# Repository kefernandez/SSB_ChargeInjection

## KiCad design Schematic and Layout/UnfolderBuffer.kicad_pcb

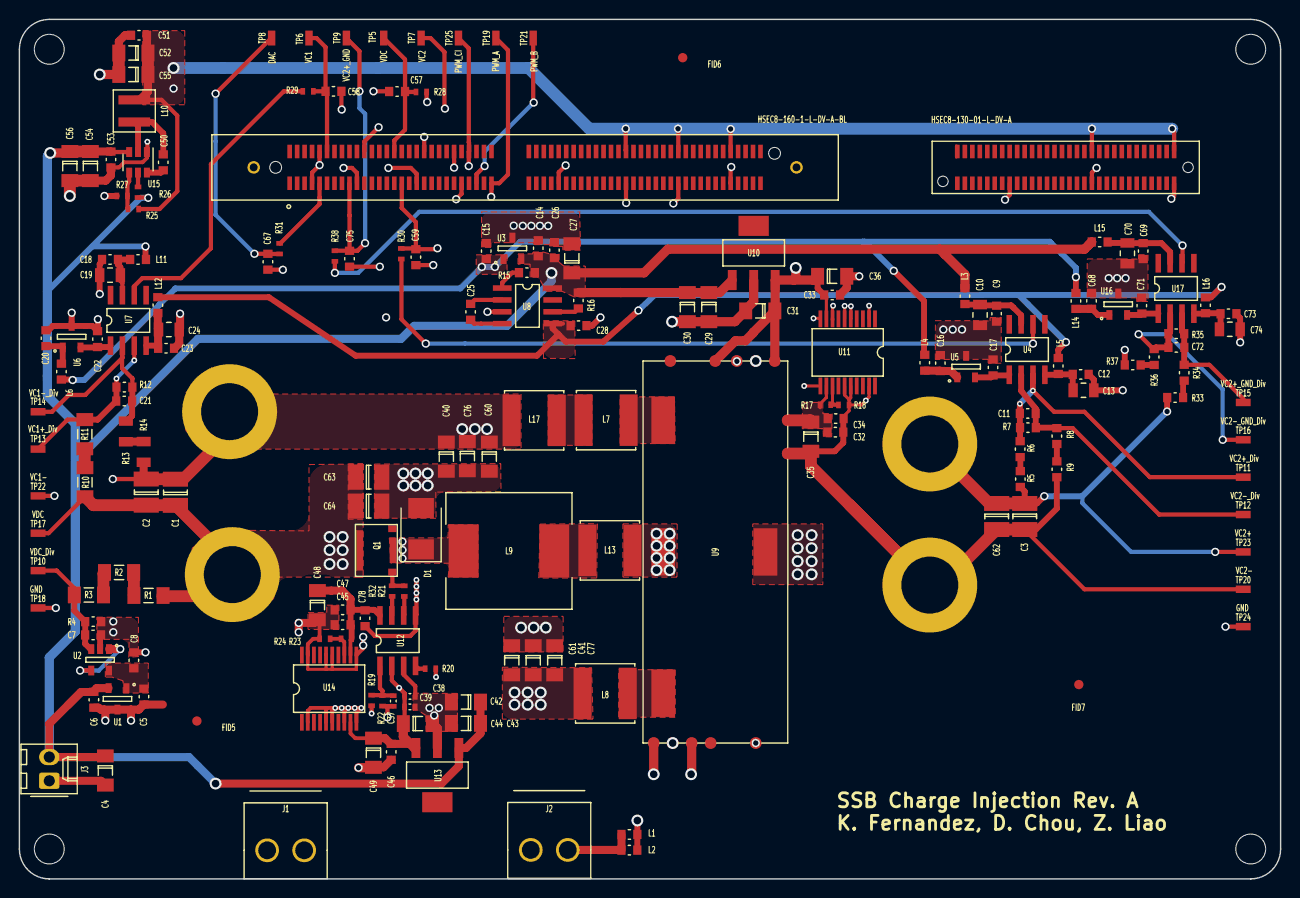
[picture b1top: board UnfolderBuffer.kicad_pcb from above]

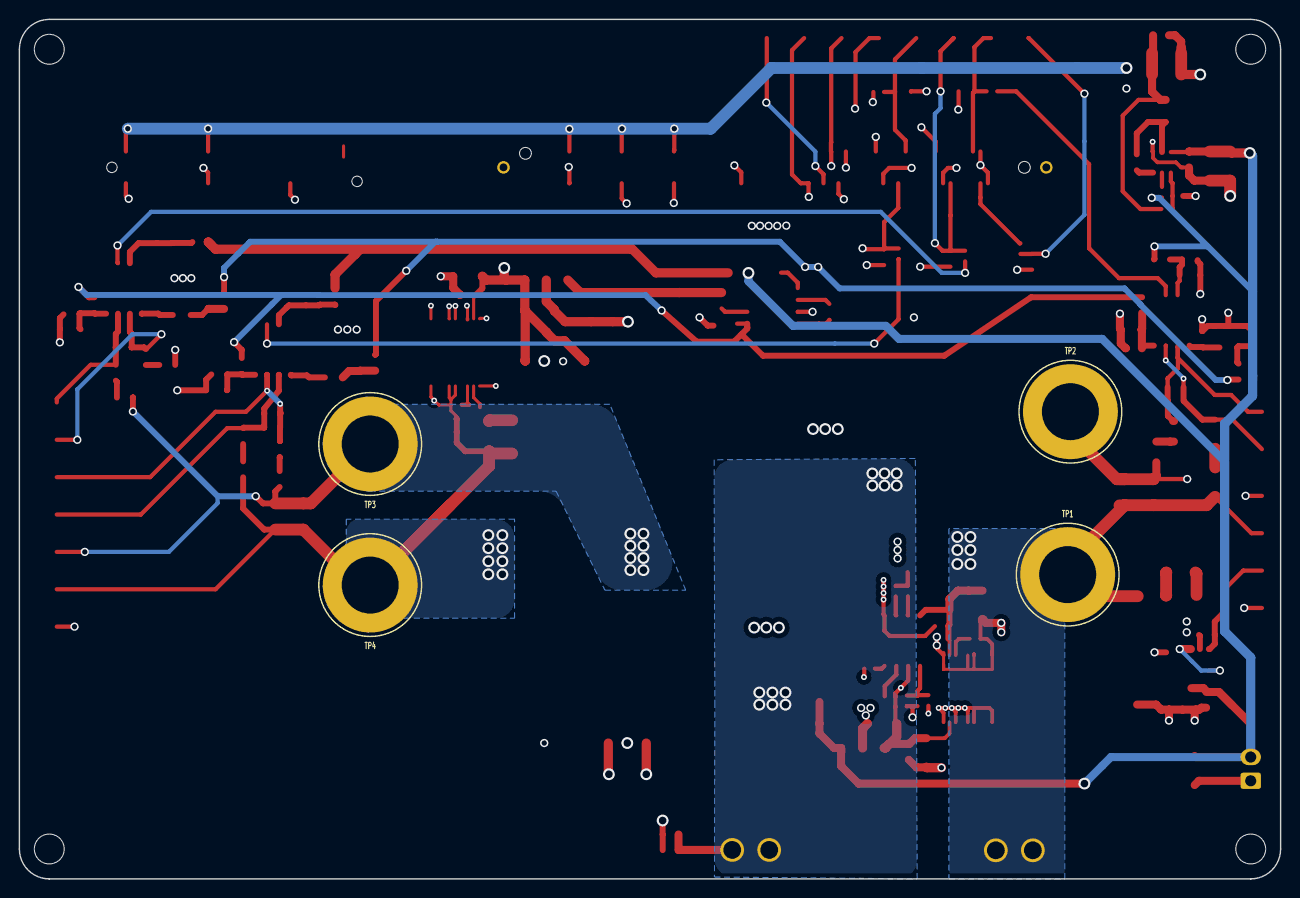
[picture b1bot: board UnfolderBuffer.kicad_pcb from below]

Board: 4 copper layers, 135.0 x 92.0 mm, 187 parts (4 on the bottom side), 75 nets.

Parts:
C1, C2: C1_sense; C_1210
C3, C62: C2_sense; C_1210
C4: 1uF; C_1206
C5, C6, C8, C9, C12, C14, C15, C16, C17, C18, C20, C22, C23, C26, C32, C45, C67, C68, C69, C71, C73, C75, C78: 1uF; C_0603
C7: 1000pF; C_0603
C10, C13, C19, C24, C70, C74: 10uF; C_0805
C11, C21, C72: 100pF; C_0603
C25, C28: 10uF; C_0603
C27, C29, C31, C35, C36, C42, C44, C48, C49, C54, C56: 10uF; C_1206
C30, C43: 0.1uF; C_1206
C33, C34, C46, C47, C50, C51, C53, C57, C59: 0.1uF; C_0603
C37: 100pF; C_0402
C38: 1uF; C_0402
C39: 0.1uF; C_0402
C40, C41, C60, C61, C76, C77: C3; C_1206
C52, C55: 22uF; C_1206
C58: .01uF; C_0603
C63, C64: Vbus_loop; C_1210
D1: D; D_SMB
FID1, FID2, FID3, FID4: Stand; MountingHole_3.2mm_M3
FID5, FID6, FID7: FID; Fiducial_1mm_Dia_2.54mm_Outer_CopperTop
J1, J2: Conn_01x02; MTA156_2pin
J3: Conn_01x02; Molex_KK-254_AE-6410-02A_1x02_P2.54mm_Vertical
J4: HSEC8-160-1-L-DV-A-BL; SAMTEC_HSEC8-160-01-L-DV-A-BL
J5: HSEC8-130-01-L-DV-A; SKT-60_flipped
L1, L2: Bead; R_0603
L3, L4, L5, L6, L11, L12, L14, L15, L16: Ferrite; C_0603
L7, L8, L17: 47uH; XAL7070
L9: 100uH; MSS1210
L10: 4.7uH; XEL4030
L13: 100uH; XAL7070
Q1: NFET_GaNSystems; GS66506T
R1, R2, R3: 470k; R_1206
R4, R15, R16: 10k; R_0603
R5, R6, R8, R9, R33, R34, R36, R37: 33k; R_0603
R7, R12, R35: 2k; R_0603
R10, R11: 44.2k; R_1206
R13, R14: 44.2k; R_0805
R17, R23: 30.9k; R_0402
R18, R24: 9.53k; R_0402
R19, R28, R29, R31, R38: 150; R_0402
R20, R32: 0; R_0402
R21: 15; R_0402
R22, R26, R27: 10k; R_0402
R25: 54.9k; R_0402
R30: 500; R_0402
TP1, TP2, TP3, TP4: TP; Banana_Jack_1Pin
TP5, TP6, TP7, TP8, TP9, TP10, TP11, TP12, TP13, TP14, TP15, TP16, TP17, TP18, TP19, TP20, TP21, TP22, TP23, TP24, TP25: TestPoint; 0603 TP
U1: TLV760 - 3.3V; SOT-23
U2: LTC2050_+; SOT-23-5
U3: TLV760; SOT-23
U4, U7, U17: LT1990; SOIC-8
U5, U6, U16: REF3012; SOT-23
U8: LTC1144; SOIC-8
U9: FullBridgeCell; Buffer Full Bridge
U10, U13: LM2937xMP; SOT223-4
U11, U14: ADuM5010; SSOP-20_Wide
U12: Si8271; SOIC-8
U15: TPS562200; SOT-23-6

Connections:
6V5: C4.1, C6.1, C14.1, C26.1, C27.1, C29.1, C30.1, C42.1, C43.1, C53.1, C54.1, C56.1, J3.2, L3.1, L11.1, L15.1, R15.2, R16.1, R26.2, U1.2, U3.2, U8.8, U10.1, U13.1, U15.3
/C1-: C1.2, C2.2, C40.1, C41.1, C60.1, C61.1, C76.1, C77.1, L17.2, R14.2, TP2.1, TP22.1
/C2+: C3.1, C62.1, L13.2, R5.1, R33.1, TP3.1, TP23.1, U9.10
/C2-: C3.2, C32.2, C34.2, C35.2, C62.2, R9.2, R18.2, TP4.1, TP20.1, U9.11, U9.13, U11.11, U11.15, U11.16, U11.19
/CI/En_CI: R20.2, U12.4
/CI/Gate_CI: Q1.G, R21.1, R32.1
/CI/L_Jumper: L9.2, L13.1
/CI/PWM_CI: C37.1, R19.2, R22.1, U12.1
/CI/VDDISO2: C45.1, C47.1, C48.1, C78.1, R23.1, U12.8, U14.12
/CI/VDD_Logic_CI: C38.1, C39.1, C44.1, C46.1, C49.1, R20.1, U12.2, U13.3, U14.9
/CI/Vo_high: R21.2, U12.7
/CI/Vo_low: R32.2, U12.6
/CI/sheet5FF6C3C6/Sel: R23.2, R24.1, U14.13
/INCI: J4.50, R19.1, TP25.1
/MCU_Connector/5V: C51.1, C52.1, C55.1, J4.84, J4.98, J4.112, J5.38, J5.60, L10.2, R25.2
/MCU_Connector/Buck_Bst: C50.2, U15.6
/MCU_Connector/Buck_FB: R25.1, R27.2, U15.4
/MCU_Connector/Buck_Sw: C50.1, L10.1, U15.2
/MCU_Connector/DACOUT: J4.9, R31.1
/MCU_Connector/DACOUT_probe: C67.1, R31.2, TP8.1
/MCU_Connector/En_Buck: R26.1, U15.5
/MCU_Connector/Vc1: C58.1, J4.12, R29.2, TP6.1
/MCU_Connector/Vc2: C59.1, J4.31, R30.2, TP7.1
/MCU_Connector/Vc2_GND: C75.1, J4.17, R38.2, TP9.1
/MCU_Connector/Vdc: C57.1, J4.30, R28.2, TP5.1
/SSB/GND_L_FB: L8.1, U9.9
/SSB/ISODCDC/Sel: R17.2, R18.1, U11.13
/SSB/LC1_FB: L7.1, U9.8
/SSB/VDDISO1: C32.1, C34.1, C35.1, R17.1, U9.12, U11.12
/SSB/VDD_Logic_FB: C31.1, C33.1, C36.1, U9.1, U9.6, U10.3, U11.9
/Sci_Source: C45.2, C47.2, C48.2, C78.2, D1.1, L9.1, Q1.S, R24.2, U12.5, U14.11, U14.15, U14.16, U14.19
/VC1_SENSE: R29.1, U7.6
/VC2_GND_SENSE: R38.1, U17.6
/VC2_SENSE: R30.1, U4.6
/VCSense/1V25_VC1SENSE: C22.1, U6.2, U7.1
/VCSense/1V25_VC2SENSE: C17.1, U4.1, U5.2
/VCSense/1V25_VC2_GND_SENSE: C71.1, U16.2, U17.1
/VCSense/5V_VC1SENSE_FIL: C20.1, L6.2, U6.1
/VCSense/5V_VC2SENSE_FIL: C16.1, L4.2, U5.1
/VCSense/5V_VC2_GND_SENSE_FIL: C68.1, L14.2, U16.1
/VCSense/5V_VCSENSE: C15.1, L4.1, L6.1, L14.1, U3.1
/VCSense/6V5_C1_FIL_SENSE: C18.1, C19.1, L11.2, U7.7
/VCSense/6V5_C2_FIL_SENSE: C9.1, C10.1, L3.2, U4.7
/VCSense/6V5_C2_GND_FIL_SENSE: C69.1, C70.1, L15.2, U17.7
/VCSense/-6V5_C1_FIL_SENSE: C23.2, C24.2, L12.1, U7.4
/VCSense/-6V5_C2_FIL_SENSE: C12.2, C13.2, L5.1, U4.4
/VCSense/-6V5_C2_GND_FIL_SENSE: C73.2, C74.2, L16.1, U17.4
/VCSense/-6V5_VCSENSE: C28.1, L5.2, L12.2, L16.2, U8.5
/VCSense/V+_C1: C21.1, R11.2, R12.1, TP13.1, U7.3
/VCSense/V+_C2: C11.1, R6.2, R7.1, TP11.1, U4.3
/VCSense/V+_C2_GND: C72.1, R34.2, R35.1, TP15.1, U17.3
/VCSense/V-_C1: C21.2, R12.2, R13.1, TP14.1, U7.2
/VCSense/V-_C2: C11.2, R7.2, R8.1, TP12.1, U4.2
/VCSense/V-_GND_C2: C72.2, R35.2, R36.1, TP16.1, U17.2
/VDC: C1.1, C2.1, C63.1, C64.1, J1.1, J1.2, Q1.D, R1.1, R10.1, TP1.1, TP17.1
/VDC/HV1_DIV: C7.1, R3.2, R4.1, TP10.1, U2.3
/VDC_SENSE: R28.1, U2.1, U2.4
/VDD_Logic_HVSense: C5.1, C8.1, U1.1, U2.5
/~INA: J4.55, TP19.1, U9.2
/~INB: J4.51, TP21.1, U9.4
GND: C4.2, C5.2, C6.2, C7.2, C8.2, C9.2, C10.2, C12.1, C13.1, C14.2, C15.2, C16.2, C17.2, C18.2, C19.2, C20.2, C22.2, C23.1, C24.1, C26.2, C27.2, C28.2, C29.2, C30.2, C31.2, C33.2, C36.2, C37.2, C38.2, C39.2, C42.2, C43.2, C44.2, C46.2, C49.2, C51.2, C52.2, C53.2, C54.2, C55.2, C56.2, C57.2, C58.2, C59.2, C67.2, C68.2, C69.2, C70.2, C71.2, C73.1, C74.1, C75.2, J3.1, J4.7, J4.10, J4.19, J4.22, J4.35, J4.38, J4.46, J4.47, J4.65, J4.83, J4.97, J4.111, J5.15, J5.37, J5.59, L1.2, L2.2, R4.2, R22.2, R27.1, R37.2, TP18.1, TP24.1, U1.3, U2.2, U3.3, U5.3, U6.3, U8.3, U9.7, U10.2, U11.2, U11.5, U11.6, U11.8, U11.10, U12.3, U13.2, U14.2, U14.5, U14.6, U14.8, U14.10, U15.1, U16.3
GNDPWR: C40.2, C41.2, C60.2, C61.2, C63.2, C64.2, C76.2, C77.2, D1.2, J2.1, J2.2, L1.1, L2.1, L8.2
unnamed: C25.1, U8.2
unnamed: C25.2, U8.4
unnamed: L7.2, L17.1
unnamed: R1.2, R2.1
unnamed: R2.2, R3.1
unnamed: R5.2, R6.1
unnamed: R8.2, R9.1
unnamed: R10.2, R11.1
unnamed: R13.2, R14.1
unnamed: R15.1, U8.1
unnamed: R16.2, U8.6
unnamed: R33.2, R34.1
unnamed: R36.2, R37.1

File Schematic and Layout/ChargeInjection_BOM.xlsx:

References | Quantity | Quanitity Ordered | Value | Footprint | Max Voltage/Current | Supplier Part Number | MFG Part No. | Supplier | Temp Coefficient | Voltage Rating |  | Notes
C37 | 1 | 50 | 100pF | C_0402 | 5V | 478-12641-1-ND | 04025C101JAT2A | Digikey | X7R | 50V
C38 | 1 | 50 | 1uF | C_0402 | 5V | 1276-1513-1-ND | CL05B105KQ5NQNC | Digikey | X7R | 6.3V
C39 | 1 | 50 | 0.1uF | C_0402 | 5V | 1276-1002-1-ND | CL05B104KP5NNNC | Digikey | X7R | 10V
C5, C6, C8, C9, C12, C14, C15, C16, C17, C18, C20, C22, C23, C26, C32, C45, C68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 | 21 | 100 | 1uF | C_0603 |  | 1276-1946-1-ND | CL10B105KP8NNNC | Digikey | X7R | 10V
C11, C21, C57, C58, C59, C67, C72, C75 | 8 | 50 | 100pF | C_0603 |  | 1276-1908-1-ND | CL10B101KB8NFNC | Digikey | X7R | 50V
C33, C34, C46, C47, C50, C51, C53 | 7 | 50 | 0.1uF | C_0603 |  | 1276-CL10B104KB8NNNLCT-ND | CL10B104KB8NNNL | Digikey | X7R | 50V
C25, C28 | 2 | 50 | 10uF | C_0603 | 6.5V | 490-14461-1-ND | GRM188D71A106KA73D | Digikey | X7T | 10V |  | Pricey
C7 | 1 | 50 | 1000pF | C_0603 | 2.8V | 1276-1018-1-ND | CL10B102KB8NNNC | Digikey | X7R | 50V
C10, C13, C19, C24, C70, C74 | 6 | 50 | 10uF | C_0805 | 6.5V | 1276-1764-1-ND | CL21B106KPQNNNE | Digikey | X7R | 10V
C27, C29, C31, C35, C36, C42, C44, C48, C49, C54, C56 | 11 | 50 | 10uF | C_1206 | 6.5V | 1276-6641-1-ND | CL31B106MOHNNNE | Digikey | X7R | 16V
C40, C41, C60, C61, C76, C77 | 6 | 50 | 1uF (C3) | C_1206 | 85V | 1276-1838-1-ND | CL31B105KCHNNNE | Digikey | X7R | 100V
C30, C43 | 2 | 30 | 0.1uF | C_1206 | 6.5V | 732-8086-1-ND | CAP CER 0.1UF 10V X7R 1206 | Digikey | X7R | 10V |  | Could have made this an 0805 or an 0603, will order some 0805s as well
C52, C55 | 2 | 30 | 22uF | C_1206 | 5V | 1276-3148-1-ND | CL31B226MPHNNNE | Digikey | X7R | 10V
C4 | 1 | 30 | 1uF | C_1206 | 6.5V | 478-12854-1-ND | 1206ZC105KAT2A | Digikey | X7R | 10V
C1, C2 | 2 | 50 | 0.1uF (C1_sense) | C_1210 | 500V | 399-15981-1-ND | C1210C104KBRACAUTO | Digikey | X7R | 630V
C3, C62 | 2 | 30 | 1uF (C2_sense) | C_1210 | 100V | 1276-1812-1-ND | CL32B105KCJNNNE | Digikey | X7R | 100V
C63, C64 | 2 |  | 0.1uF (Vbus_loop) | C_1210 | 400V | 399-15981-1-ND | C1210C104KBRACAUTO | Digikey | X7R | 630V
R28, R29, R30, R31, R38 | 5 | 30 | 499 | R_0402 |  | P499DCCT-ND | ERA-2AEB4990X | Digikey |  | 1/16W
R22, R26, R27 | 3 | 30 | 10k | R_0402 |  | MCS0402-10.0K-MFCT-ND | MCS0402MC1002FE000 | Digikey |  | 1/10W
R17, R23 | 2 | 20 | 30.9k | R_0402 | 16nA, 0.5 mW | P18022CT-ND | ERA-2ARB3092X | Digikey |  | 1/16W | 1E-3
R18, R24 | 2 | 20 | 9.53k | R_0402 | 16nA, 0.2mW | P17916CT-ND | ERA-2APB9531X | Digikey |  | 1/16W | 1E-3
R20, R32 | 2 | 30 | 0 | R_0402 |  | 541-0.0JCT-ND | CRCW04020000Z0ED | Digikey |  | 1/16W
R19 | 1 | 30 | 150 | R_0402 |  | P150DCCT-ND | ERA-2AEB151X | Digikey |  | 1/16W | 1E-3
R21 | 1 | 30 | 15 | R_0402 |  | P15DDCT-ND | ERA-2AKD150X | Digikey |  | 1/16W | 5.0000000000000001E-3
R25 | 1 | 20 | 54.9k | R_0402 |  | YAG1452CT-ND | RT0402BRD0754K9L | Digikey |  | 1/16W | 1E-3
R5, R6, R8, R9, R33, R34, R36, R37 | 8 | 25 | 33k | R_0603 | 0.05W | P20143CT-ND | ERJ-PB3B3302V | Digikey |  | 1/5W | 1E-3
R4, R15, R16 | 3 | 30 | 10k | R_0603 | 0.8mW | P10KDBCT-ND | ERA-3AEB103V | Digikey |  | 1/10W | 1E-3
R7, R12, R35 | 3 | 30 | 2k | R_0603 | 0.5mW | RG16P2.0KBCT-ND | RG1608P-202-B-T5 | Digikey |  | 1/10W | 1E-3
R13, R14 | 2 | 20 | 16k | R_0805 | 0.04W | P16KDACT-ND | ERA-6AEB163V | Digikey |  | 1/8W | 1E-3
R1, R2, R3 | 3 | 30 | 470k | R_1206 | 0.04W | P470KBCCT-ND | ERA-8AEB474V | Digikey |  | 1/4W | 1E-3
R10, R11 | 2 | 30 | 150k | R_1206 | 0.35W | RHM150KAFCT-ND | ESR18EZPF1503 | Digikey |  | 1/2W | 1E-3
L3, L4, L5, L6, L11, L12, L14, L15, L16 | 9 | 50 | Ferrite | C_0603 | 1.2E-4 | 732-1592-1-ND | 742792641 | Digikey |  | 2A
L9 | 1 | 10 | 100uH | MSS1210 | 1.2A | 994-MSS1210-104KEB | MSS1210-104KEB | Mouser
L1, L2 | 2 |  | Bead | R_0603 |  | 732-1592-1-ND | 742792641 | Digikey
L7, L8, L17 | 3 | 20 | 47uH | XAL7070 |  | XAL7070-473MEC | XAL7070-473MEC | Coilcraft
L13 - DNP - Jumper | 0 | X | 100uH | XAL7070 |  |  |  | N/A
L10 - Derek has several in lab | 1 | X | 4.7uH | XEL4030 |  | 994-XAL7070-472MEB | XAL7070-472MEB | N/A
D1 | 1 | 15 | D | D_SMB |  | MURS160T3GOSCT-ND | MURS160T3G | Digikey
U9 | 1 | X | FullBridgeCell | Buffer Full Bridge
U4, U7, U17 | 3 | 12 | LT1990 | SOIC-8 |  | LT1990CS8#PBF-ND | LT1990CS8#PBF | Digikey
U8 | 1 | 6 | LTC1144 | SOIC-8 |  | LTC1144CS8#PBF-ND | LTC1144CS8#PBF | Digikey
U12 | 1 | 10 | Si8271 | SOIC-8 |  | 336-3533-5-ND | SI8271GB-IS | Digikey
U5, U6, U16 | 3 | 15 | REF3012 | SOT-23 |  | 296-32213-1-ND | REF3012AIDBZR | Digikey
U1, U3 | 2 | 12 | TLV760 - 5V | SOT-23 |  | 296-48333-1-ND | TLV76050DBZR | Digikey
 | 2 | 12 | TLV760 - 3.3V | SOT-23 |  | 296-47016-1-ND | TLV76033DBZT | Digikey
U2 | 1 | 6 | LTC2050_+ | SOT-23-5 |  | LTC2050CS8#PBF-ND | LTC2050CS8#PBF | Digikey
U15 | 1 | 10 | TPS562200 | SOT-23-6 |  | 296-39631-1-ND | TPS562200DDCR | Digikey
U10, U13 | 2 | 10 | LM2937xMP | SOT223-4 |  | LM2937IMP-5.0/NOPBCT-ND | LM2937IMP-5.0/NOPB | Digikey
U11, U14 | 2 | 6 | ADuM5010 | SSOP-20_Wide |  | ADUM5010ARSZ-RL7CT-ND | ADUM5010ARSZ-RL7 | Digikey
TP5, TP6, TP7, TP8, TP9, TP10, TP11, TP12, TP13, TP14, TP15, TP16, TP17, TP18, 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 | 21 | 80 | TestPoint | 0603 TP |  | A106145CT-ND | RCU-0C | Digikey
TP1, TP2, TP3, TP4 | 4 | 10 | TP | Banana_Jack_1Pin |  | BKCT2232-2-ND | CT2232-2 | Digikey
Q1 | 1 | 10 | NFET_GaNSystems | GS66506T |  | 499-GS66506T-MR | GS66506T-MR | Mouser
J1, J2 | 2 | 6 | Conn_01x02 | MTA156_2pin |  | A105038-ND | 3-641209-4 | Digikey
J3 | 1 | 5 | Conn_01x02 | Molex_KK-254_AE-6410-02A_1x02_P2.54mm_Vertical |  | A26564-ND | 1-87215-0 | Digikey
J4 | 1 | 2 | HSEC8-160-1-L-DV-A-BL | SAMTEC_HSEC8-160-01-L-DV-A-BL |  | SAM9083-ND | HSEC8-160-01-L-DV-A-BL | Digikey
J5 | 1 | 2 | HSEC8-130-01-L-DV-A | SKT-60_flipped |  | SAM9080-ND | HSEC8-130-01-L-DV-A | Digikey
C_1 | 2 | 2 | C1 |  |  | 495-3956-ND | B32776G4406K000
C_2 | 3 | 3 | C2 |  |  | 495-4131-ND | B32524Q1686K000
MCU | 1 | 1 | ControlCARD |  |  | 296-46777-ND | TMDSCNCD28379D

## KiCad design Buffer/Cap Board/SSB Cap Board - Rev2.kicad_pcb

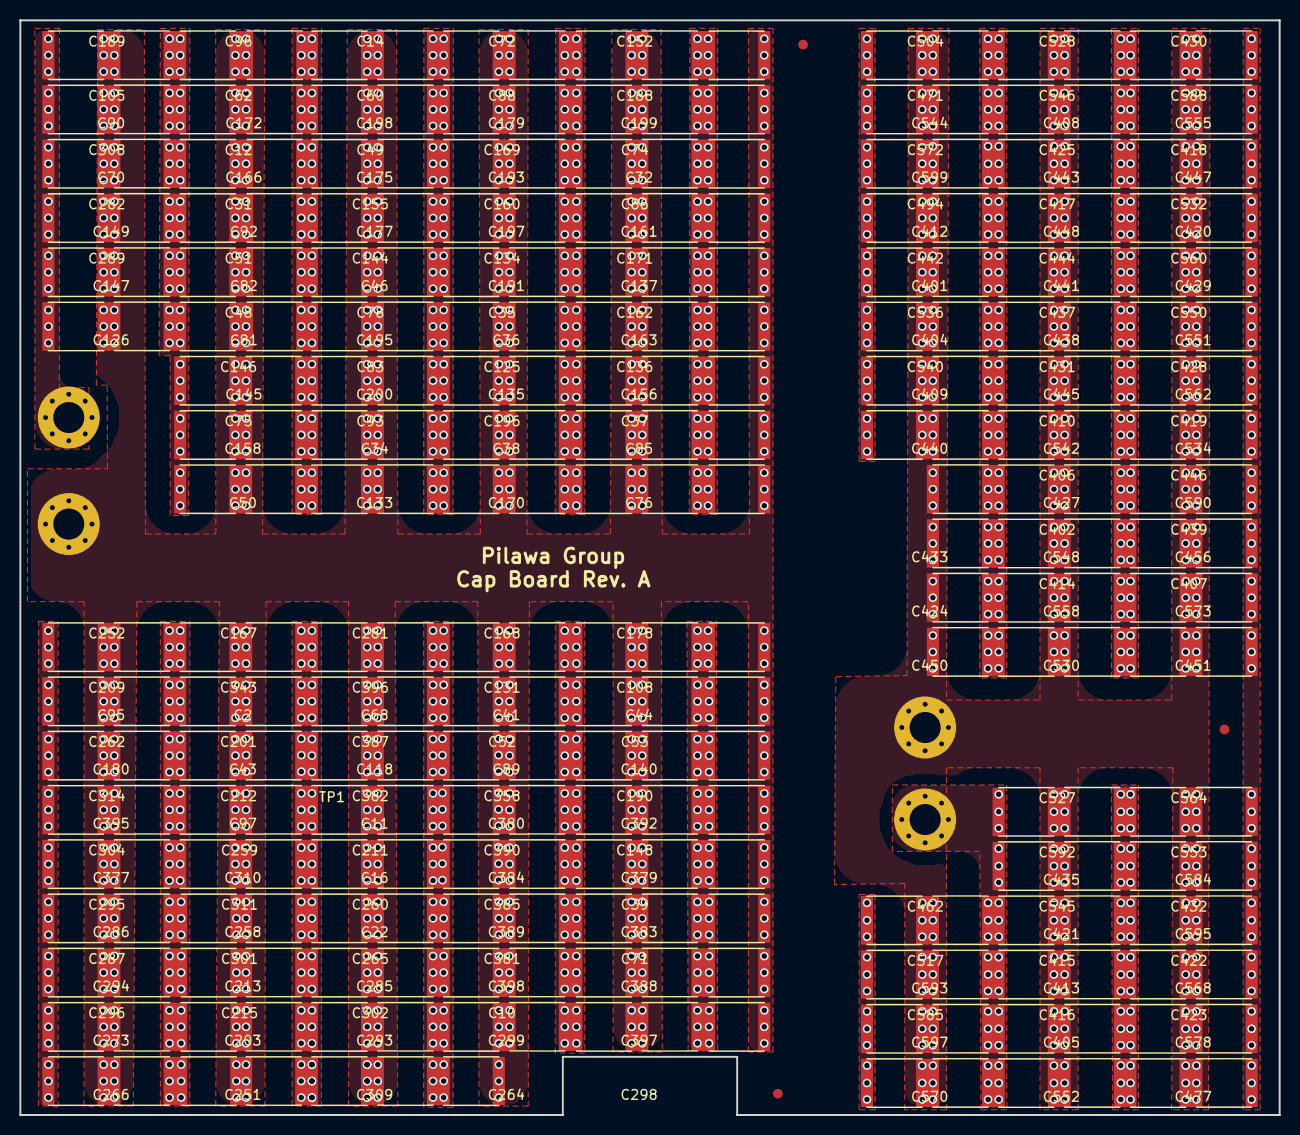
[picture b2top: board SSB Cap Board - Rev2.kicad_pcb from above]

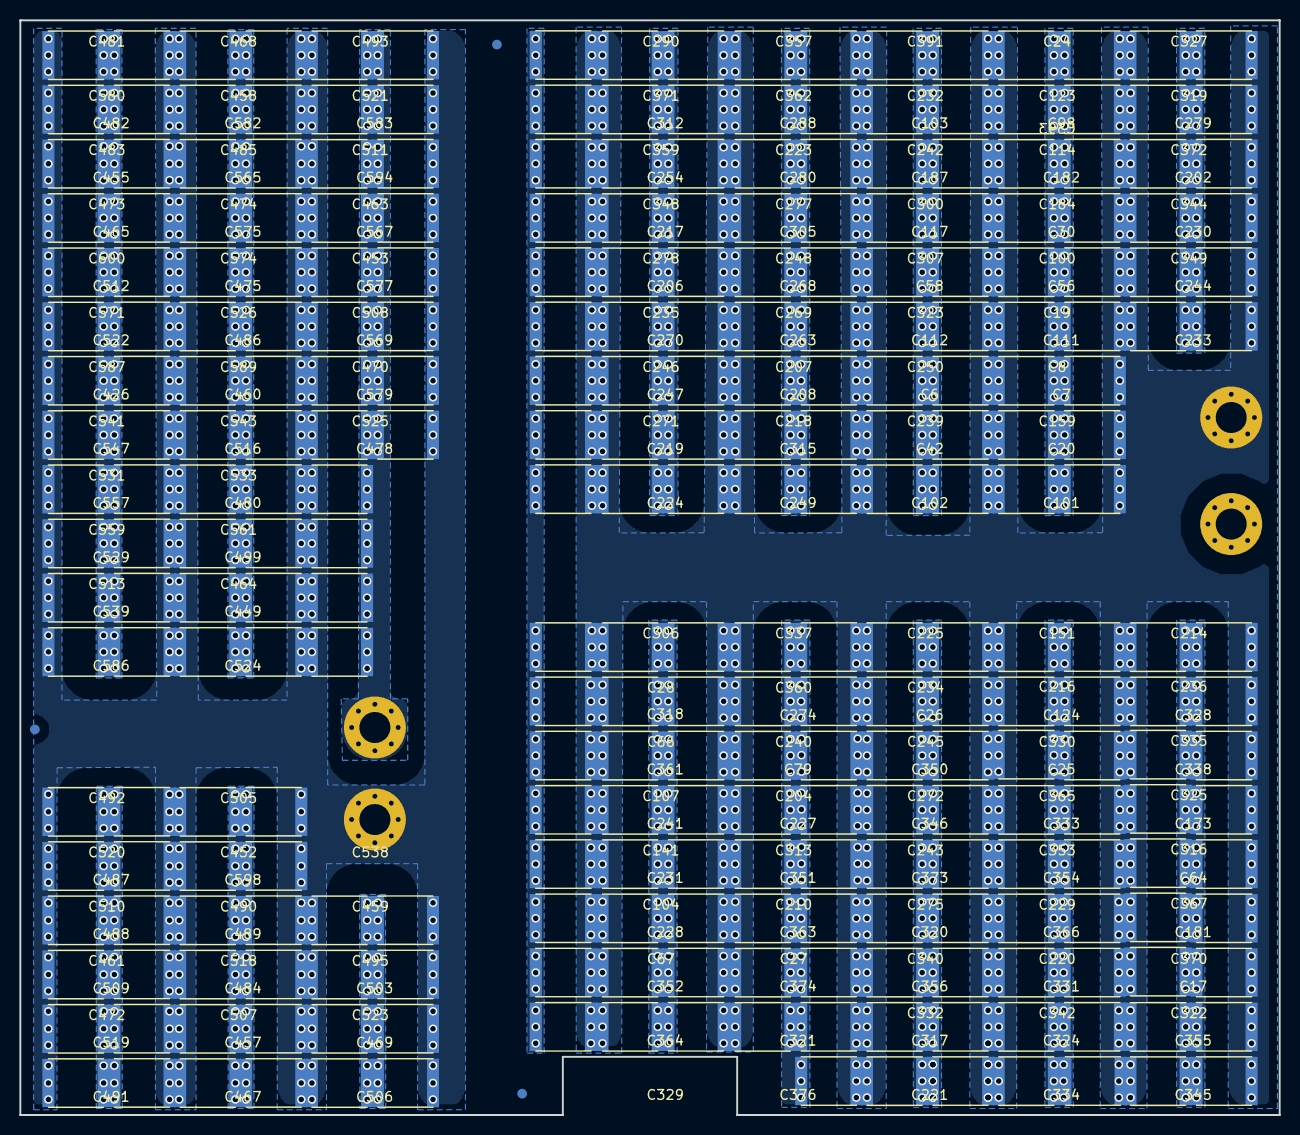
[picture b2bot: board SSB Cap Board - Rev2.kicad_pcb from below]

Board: 2 copper layers, 130.0 x 113.0 mm, 580 parts (288 on the bottom side), 4 nets, no tracks yet.

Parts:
C2, C3, C4, C5, C6, C7, C8, C9, C10, C11, C12, C14, C15, C16, C17, C18, C19, C20, C21, C22, C23, C24, C25, C26, C27, C28, C30, C31, C32, C34, C35, C36, C37, C38, C39, C40, C41, C42, C43, C44, C45, C46, C48, C49, C50, C51, C52, C53, C54, C56, C57, C58, C59, C60, C61, C62, C63, C64, C66, C67, C68, C69, C70, C71, C72, C74, C75, C76, C77, C78, C79, C80, C81, C82, C83, C84, C85, C86, C87, C88, C89, C90, C91, C92, C93, C94, C95, C96, C97, C98, C99, C100, C101, C102, C103, C104, C105, C106, C107, C108, C109, C111, C112, C113, C114, C117, C118, C119, C120, C121, C122, C123, C124, C125, C126, C129, C130, C131, C132, C133, C134, C135, C136, C137, C140, C141, C142, C143, C144, C145, C146, C147, C148, C149, C150, C151, C152, C154, C155, C156, C157, C158, C159, C160, C161, C162, C163, C164, C166, C167, C168, C169, C170, C171, C172, C173, C174, C175, C176, C177, C178, C179, C180, C181, C182, C183, C184, C185, C186, C187, C188, C189, C190, C191, C193, C194, C195, C196, C197, C198, C199, C200, C201, C202, C203, C204, C205, C206, C207, C208, C209, C210, C211, C212, C213, C214, C215, C216, C217, C218, C219, C220, C221, C223, C224, C225, C226, C227, C228, C229, C230, C231, C232, C233, C234, C235, C236, C237, C238, C239, C240, C241, C242, C243, C244, C245, C246, C247, C248, C249, C250, C251, C252, C254, C255, C256, C257, C258, C259, C260, C261, C262, C263, C264, C265, C266, C267, C268, C269, C270, C271, C272, C273, C274, C275, C276, C277, C278, C279, C280, C281, C282, C283, C285, C286, C287, C288, C289, C290, C291, C292, C293, C294, C295, C296, C297, C298, C299, C300, C301, C302, C303, C304, C305, C306, C307, C308, C309, C310, C311, C312, C313, C314, C315, C316, C317, C318, C319, C320, C321, C322, C323, C324, C325, C326, C327, C328, C329, C330, C331, C332, C333, C334, C335, C336, C337, C338, C339, C340, C341, C342, C343, C344, C345, C346, C347, C348, C349, C350, C351, C352, C353, C354, C355, C356, C357, C358, C359, C360, C361, C362, C363, C364, C365, C366, C367, C368, C369, C370, C371, C372, C373, C374, C375, C376, C377, C378, C379, C380, C381, C382, C383, C384, C385, C387, C388, C389, C390, C391, C392, C393, C394, C395, C396, C397, C398, C401, C402, C403, C404, C405, C406, C407, C408, C409, C410, C411, C412, C413, C414, C415, C416, C417, C418, C419, C420, C421, C422, C423, C424, C425, C426, C427, C428, C429, C430, C431, C432, C433, C434, C435, C436, C437, C438, C439, C440, C441, C442, C443, C444, C445, C446, C447, C448, C449, C450, C451, C452, C453, C454, C455, C456, C457, C458, C459, C460, C461, C462, C463, C464, C465, C466, C467, C468, C469, C470, C471, C472, C473, C474, C475, C476, C477, C478, C479, C480, C481, C482, C483, C484, C485, C486, C487, C488, C489, C490, C491, C492, C493, C494, C495, C496, C497, C498, C499, C500, C501, C502, C503, C504, C505, C506, C507, C508, C509, C510, C511, C512, C513, C514, C515, C516, C517, C518, C519, C520, C521, C522, C523, C524, C525, C526, C527, C528, C529, C530, C531, C532, C533, C534, C535, C536, C537, C538, C539, C540, C541, C542, C543, C544, C545, C546, C547, C548, C549, C550, C551, C552, C553, C554, C555, C556, C557, C558, C559, C560, C561, C562, C563, C564, C565, C566, C567, C568, C569, C570, C571, C572, C573, C574, C575, C576, C577, C578, C579, C580, C581, C582, C583, C584, C585, C586, C587, C588, C589, C590, C591, C592, C593, C594, C595, C596, C597, C598, C599, C600: 2.2 uF; C_2220_Sm
TP1, TP2, TP3, TP4: TestPoint; MountingHole_3.2mm_M3_Pad_Via

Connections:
/C1+: C2.1, C3.1, C4.1, C5.1, C6.1, C7.1, C8.1, C9.1, C10.1, C11.1, C12.1, C14.1, C15.1, C16.1, C17.1, C18.1, C19.1, C20.1, C21.1, C22.1, C23.1, C24.1, C25.1, C26.1, C27.1, C28.1, C30.1, C31.1, C32.1, C34.1, C35.1, C36.1, C37.1, C38.1, C39.1, C40.1, C41.1, C42.1, C43.1, C44.1, C45.1, C46.1, C48.1, C49.1, C50.1, C51.1, C52.1, C53.1, C54.1, C56.1, C57.1, C58.1, C59.1, C60.1, C61.1, C62.1, C63.1, C64.1, C66.1, C67.1, C68.1, C69.1, C70.1, C71.1, C72.1, C74.1, C75.1, C76.1, C77.1, C78.1, C79.1, C80.1, C81.1, C82.1, C83.1, C84.1, C85.1, C86.1, C87.1, C88.1, C89.1, C90.1, C91.1, C92.1, C93.1, C94.1, C95.1, C96.1, C97.1, C98.1, C99.1, C100.1, C101.1, C102.1, C103.1, C104.1, C105.1, C106.1, C107.1, C108.1, C109.1, C111.1, C112.1, C113.1, C114.1, C117.1, C118.1, C119.1, C120.1, C121.1, C122.1, C123.1, C124.1, C125.1, C126.1, C129.1, C130.1, C131.1, C132.1, C133.1, C134.1, C135.1, C136.1, C137.1, C140.1, C141.1, C142.1, C143.1, C144.1, C145.1, C146.1, C147.1, C148.1, C149.1, C150.1, C151.1, C152.1, C154.1, C155.1, C156.1, C157.1, C158.1, C159.1, C160.1, C161.1, C162.1, C163.1, C164.1, C166.1, C167.1, C168.1, C169.1, C170.1, C171.1, C172.1, C173.1, C174.1, C175.1, C176.1, C177.1, C178.1, C179.1, C180.1, C181.1, C182.1, C183.1, C184.1, C185.1, C186.1, C187.1, C188.1, C189.1, C190.1, C191.1, C193.1, C194.1, C195.1, C196.1, C197.1, C198.1, C199.1, C200.1, C201.1, C202.1, C203.1, C204.1, C205.1, C206.1, C207.1, C208.1, C209.1, C210.1, C211.1, C212.1, C213.1, C214.1, C215.1, C216.1, C217.1, C218.1, C219.1, C220.1, C221.1, C223.1, C224.1, C225.1, C226.1, C227.1, C228.1, C229.1, C230.1, C231.1, C232.1, C233.1, C234.1, C235.1, C236.1, C237.1, C238.1, C239.1, C240.1, C241.1, C242.1, C243.1, C244.1, C245.1, C246.1, C247.1, C248.1, C249.1, C250.1, C251.1, C252.1, C254.1, C255.1, C256.1, C257.1, C258.1, C259.1, C260.1, C261.1, C262.1, C263.1, C264.1, C265.1, C266.1, C267.1, C268.1, C269.1, C270.1, C271.1, C272.1, C273.1, C274.1, C275.1, C276.1, C277.1, C278.1, C279.1, C280.1, C281.1, C282.1, C283.1, C285.1, C286.1, C287.1, C288.1, C289.1, C290.1, C291.1, C292.1, C293.1, C294.1, C295.1, C296.1, C297.1, C298.1, C299.1, C300.1, C301.1, C302.1, C303.1, C304.1, C305.1, C306.1, C307.1, C308.1, C309.1, C310.1, C311.1, C312.1, C313.1, C314.1, C315.1, C316.1, C317.1, C318.1, C319.1, C320.1, C321.1, C322.1, C323.1, C324.1, C325.1, C326.1, C327.1, C328.1, C329.1, C330.1, C331.1, C332.1, C333.1, C334.1, C335.1, C336.1, C337.1, C338.1, C339.1, C340.1, C341.1, C342.1, C343.1, C344.1, C345.1, C346.1, C347.1, C348.1, C349.1, C350.1, C351.1, C352.1, C353.1, C354.1, C355.1, C356.1, C357.1, C358.1, C359.1, C360.1, C361.1, C362.1, C363.1, C364.1, C365.1, C366.1, C367.1, C368.1, C369.1, C370.1, C371.1, C372.1, C373.1, C374.1, C375.1, C376.1, C377.1, C378.1, C379.1, C380.1, C381.1, C382.1, C383.1, C384.1, C385.1, C387.1, C388.1, C389.1, C390.1, C391.1, C392.1, C393.1, C394.1, C395.1, C396.1, C397.1, C398.1, TP1.1
/C1-: C2.2, C3.2, C4.2, C5.2, C6.2, C7.2, C8.2, C9.2, C10.2, C11.2, C12.2, C14.2, C15.2, C16.2, C17.2, C18.2, C19.2, C20.2, C21.2, C22.2, C23.2, C24.2, C25.2, C26.2, C27.2, C28.2, C30.2, C31.2, C32.2, C34.2, C35.2, C36.2, C37.2, C38.2, C39.2, C40.2, C41.2, C42.2, C43.2, C44.2, C45.2, C46.2, C48.2, C49.2, C50.2, C51.2, C52.2, C53.2, C54.2, C56.2, C57.2, C58.2, C59.2, C60.2, C61.2, C62.2, C63.2, C64.2, C66.2, C67.2, C68.2, C69.2, C70.2, C71.2, C72.2, C74.2, C75.2, C76.2, C77.2, C78.2, C79.2, C80.2, C81.2, C82.2, C83.2, C84.2, C85.2, C86.2, C87.2, C88.2, C89.2, C90.2, C91.2, C92.2, C93.2, C94.2, C95.2, C96.2, C97.2, C98.2, C99.2, C100.2, C101.2, C102.2, C103.2, C104.2, C105.2, C106.2, C107.2, C108.2, C109.2, C111.2, C112.2, C113.2, C114.2, C117.2, C118.2, C119.2, C120.2, C121.2, C122.2, C123.2, C124.2, C125.2, C126.2, C129.2, C130.2, C131.2, C132.2, C133.2, C134.2, C135.2, C136.2, C137.2, C140.2, C141.2, C142.2, C143.2, C144.2, C145.2, C146.2, C147.2, C148.2, C149.2, C150.2, C151.2, C152.2, C154.2, C155.2, C156.2, C157.2, C158.2, C159.2, C160.2, C161.2, C162.2, C163.2, C164.2, C166.2, C167.2, C168.2, C169.2, C170.2, C171.2, C172.2, C173.2, C174.2, C175.2, C176.2, C177.2, C178.2, C179.2, C180.2, C181.2, C182.2, C183.2, C184.2, C185.2, C186.2, C187.2, C188.2, C189.2, C190.2, C191.2, C193.2, C194.2, C195.2, C196.2, C197.2, C198.2, C199.2, C200.2, C201.2, C202.2, C203.2, C204.2, C205.2, C206.2, C207.2, C208.2, C209.2, C210.2, C211.2, C212.2, C213.2, C214.2, C215.2, C216.2, C217.2, C218.2, C219.2, C220.2, C221.2, C223.2, C224.2, C225.2, C226.2, C227.2, C228.2, C229.2, C230.2, C231.2, C232.2, C233.2, C234.2, C235.2, C236.2, C237.2, C238.2, C239.2, C240.2, C241.2, C242.2, C243.2, C244.2, C245.2, C246.2, C247.2, C248.2, C249.2, C250.2, C251.2, C252.2, C254.2, C255.2, C256.2, C257.2, C258.2, C259.2, C260.2, C261.2, C262.2, C263.2, C264.2, C265.2, C266.2, C267.2, C268.2, C269.2, C270.2, C271.2, C272.2, C273.2, C274.2, C275.2, C276.2, C277.2, C278.2, C279.2, C280.2, C281.2, C282.2, C283.2, C285.2, C286.2, C287.2, C288.2, C289.2, C290.2, C291.2, C292.2, C293.2, C294.2, C295.2, C296.2, C297.2, C298.2, C299.2, C300.2, C301.2, C302.2, C303.2, C304.2, C305.2, C306.2, C307.2, C308.2, C309.2, C310.2, C311.2, C312.2, C313.2, C314.2, C315.2, C316.2, C317.2, C318.2, C319.2, C320.2, C321.2, C322.2, C323.2, C324.2, C325.2, C326.2, C327.2, C328.2, C329.2, C330.2, C331.2, C332.2, C333.2, C334.2, C335.2, C336.2, C337.2, C338.2, C339.2, C340.2, C341.2, C342.2, C343.2, C344.2, C345.2, C346.2, C347.2, C348.2, C349.2, C350.2, C351.2, C352.2, C353.2, C354.2, C355.2, C356.2, C357.2, C358.2, C359.2, C360.2, C361.2, C362.2, C363.2, C364.2, C365.2, C366.2, C367.2, C368.2, C369.2, C370.2, C371.2, C372.2, C373.2, C374.2, C375.2, C376.2, C377.2, C378.2, C379.2, C380.2, C381.2, C382.2, C383.2, C384.2, C385.2, C387.2, C388.2, C389.2, C390.2, C391.2, C392.2, C393.2, C394.2, C395.2, C396.2, C397.2, C398.2, TP2.1
/C2+: C401.1, C402.1, C403.1, C404.1, C405.1, C406.1, C407.1, C408.1, C409.1, C410.1, C411.1, C412.1, C413.1, C414.1, C415.1, C416.1, C417.1, C418.1, C419.1, C420.1, C421.1, C422.1, C423.1, C424.1, C425.1, C426.1, C427.1, C428.1, C429.1, C430.1, C431.1, C432.1, C433.1, C434.1, C435.1, C436.1, C437.1, C438.1, C439.1, C440.1, C441.1, C442.1, C443.1, C444.1, C445.1, C446.1, C447.1, C448.1, C449.1, C450.1, C451.1, C452.1, C453.1, C454.1, C455.1, C456.1, C457.1, C458.1, C459.1, C460.1, C461.1, C462.1, C463.1, C464.1, C465.1, C466.1, C467.1, C468.1, C469.1, C470.1, C471.1, C472.1, C473.1, C474.1, C475.1, C476.1, C477.1, C478.1, C479.1, C480.1, C481.1, C482.1, C483.1, C484.1, C485.1, C486.1, C487.1, C488.1, C489.1, C490.1, C491.1, C492.1, C493.1, C494.1, C495.1, C496.1, C497.1, C498.1, C499.1, C500.1, C501.1, C502.1, C503.1, C504.1, C505.1, C506.1, C507.1, C508.1, C509.1, C510.1, C511.1, C512.1, C513.1, C514.1, C515.1, C516.1, C517.1, C518.1, C519.1, C520.1, C521.1, C522.1, C523.1, C524.1, C525.1, C526.1, C527.1, C528.1, C529.1, C530.1, C531.1, C532.1, C533.1, C534.1, C535.1, C536.1, C537.1, C538.1, C539.1, C540.1, C541.1, C542.1, C543.1, C544.1, C545.1, C546.1, C547.1, C548.1, C549.1, C550.1, C551.1, C552.1, C553.1, C554.1, C555.1, C556.1, C557.1, C558.1, C559.1, C560.1, C561.1, C562.1, C563.1, C564.1, C565.1, C566.1, C567.1, C568.1, C569.1, C570.1, C571.1, C572.1, C573.1, C574.1, C575.1, C576.1, C577.1, C578.1, C579.1, C580.1, C581.1, C582.1, C583.1, C584.1, C585.1, C586.1, C587.1, C588.1, C589.1, C590.1, C591.1, C592.1, C593.1, C594.1, C595.1, C596.1, C597.1, C598.1, C599.1, C600.1, TP3.1
/C2-: C401.2, C402.2, C403.2, C404.2, C405.2, C406.2, C407.2, C408.2, C409.2, C410.2, C411.2, C412.2, C413.2, C414.2, C415.2, C416.2, C417.2, C418.2, C419.2, C420.2, C421.2, C422.2, C423.2, C424.2, C425.2, C426.2, C427.2, C428.2, C429.2, C430.2, C431.2, C432.2, C433.2, C434.2, C435.2, C436.2, C437.2, C438.2, C439.2, C440.2, C441.2, C442.2, C443.2, C444.2, C445.2, C446.2, C447.2, C448.2, C449.2, C450.2, C451.2, C452.2, C453.2, C454.2, C455.2, C456.2, C457.2, C458.2, C459.2, C460.2, C461.2, C462.2, C463.2, C464.2, C465.2, C466.2, C467.2, C468.2, C469.2, C470.2, C471.2, C472.2, C473.2, C474.2, C475.2, C476.2, C477.2, C478.2, C479.2, C480.2, C481.2, C482.2, C483.2, C484.2, C485.2, C486.2, C487.2, C488.2, C489.2, C490.2, C491.2, C492.2, C493.2, C494.2, C495.2, C496.2, C497.2, C498.2, C499.2, C500.2, C501.2, C502.2, C503.2, C504.2, C505.2, C506.2, C507.2, C508.2, C509.2, C510.2, C511.2, C512.2, C513.2, C514.2, C515.2, C516.2, C517.2, C518.2, C519.2, C520.2, C521.2, C522.2, C523.2, C524.2, C525.2, C526.2, C527.2, C528.2, C529.2, C530.2, C531.2, C532.2, C533.2, C534.2, C535.2, C536.2, C537.2, C538.2, C539.2, C540.2, C541.2, C542.2, C543.2, C544.2, C545.2, C546.2, C547.2, C548.2, C549.2, C550.2, C551.2, C552.2, C553.2, C554.2, C555.2, C556.2, C557.2, C558.2, C559.2, C560.2, C561.2, C562.2, C563.2, C564.2, C565.2, C566.2, C567.2, C568.2, C569.2, C570.2, C571.2, C572.2, C573.2, C574.2, C575.2, C576.2, C577.2, C578.2, C579.2, C580.2, C581.2, C582.2, C583.2, C584.2, C585.2, C586.2, C587.2, C588.2, C589.2, C590.2, C591.2, C592.2, C593.2, C594.2, C595.2, C596.2, C597.2, C598.2, C599.2, C600.2, TP4.1

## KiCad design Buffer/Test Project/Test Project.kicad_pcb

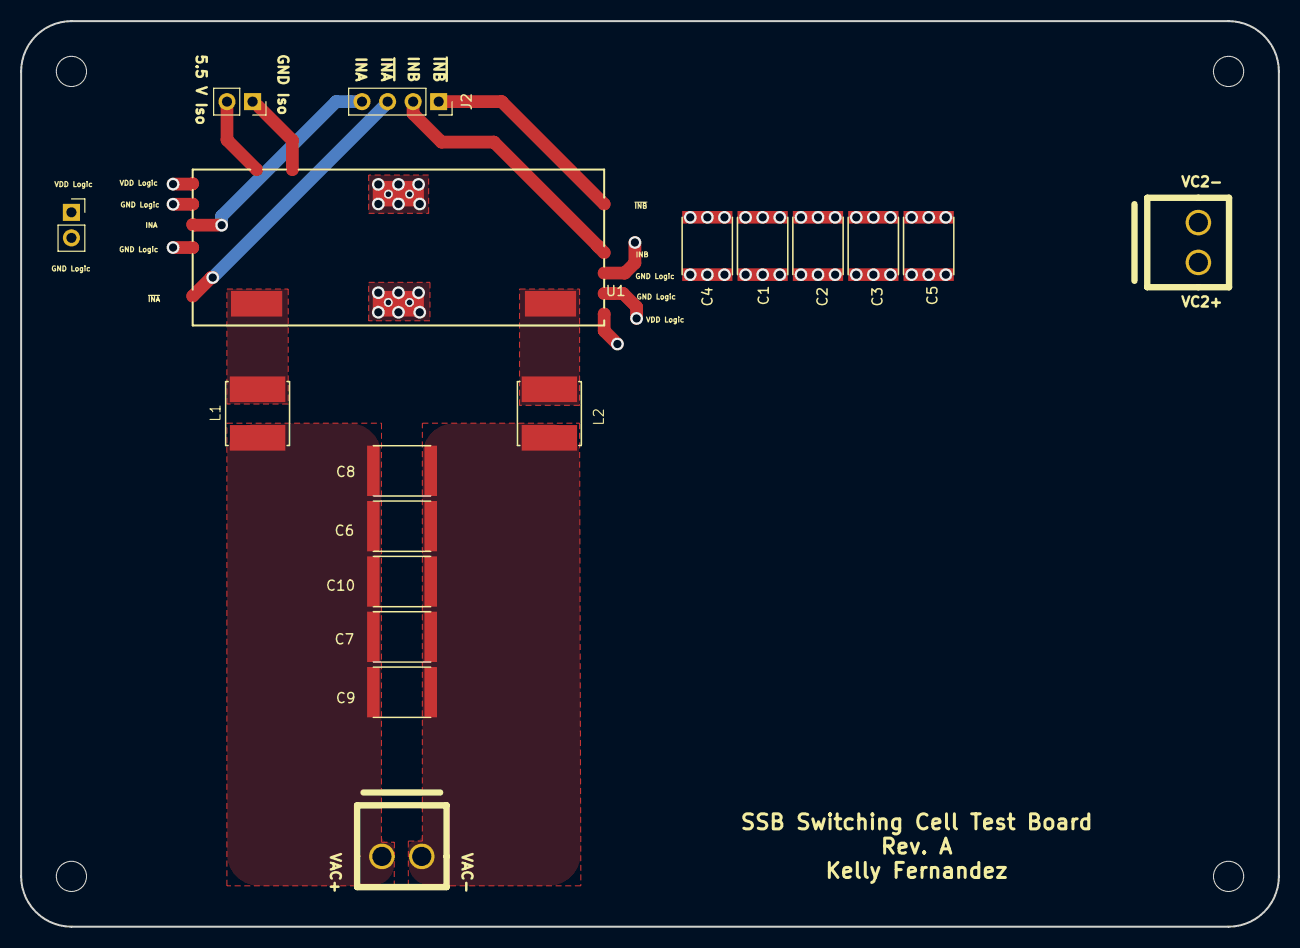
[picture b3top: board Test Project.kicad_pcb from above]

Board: 4 copper layers, 125.0 x 90.0 mm, 18 parts (0 on the bottom side), 14 nets.

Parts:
C1, C2, C3, C4, C5, C6, C7, C8, C9, C10: C; C_2220_Sm
J1, J4: Conn_01x02; MTA156_2pin
J2: Conn_01x04; PinSocket_1x04_P2.54mm_Vertical
J3, J5: Conn_01x02; PinSocket_1x02_P2.54mm_Vertical
L1, L2: L; XAL7070
U1: FullBridgeCell; Buffer Full Bridge

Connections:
/CF_Neg: L2.2, U1.9
/GND_ISO: J5.1, U1.13
/GND_Logic: J3.2, U1.6, U1.7
/INA: J2.4, U1.2
/INB: J2.2, U1.5
/LC1_Pos: L1.1, U1.8
/VAC_Neg: C6.2, C7.2, C8.2, C9.2, C10.2, J1.2, L2.1
/VAC_Pos: C6.1, C7.1, C8.1, C9.1, C10.1, J1.1, L1.2
/VC2_Neg: C1.2, C2.2, C3.2, C4.2, C5.2, J4.2, U1.11
/VC2_Pos: C1.1, C2.1, C3.1, C4.1, C5.1, J4.1, U1.10
/VDD_ISO: J5.2, U1.12
/VDD_Logic: J3.1, U1.1
/~INA: J2.3, U1.3
/~INB: J2.1, U1.4
